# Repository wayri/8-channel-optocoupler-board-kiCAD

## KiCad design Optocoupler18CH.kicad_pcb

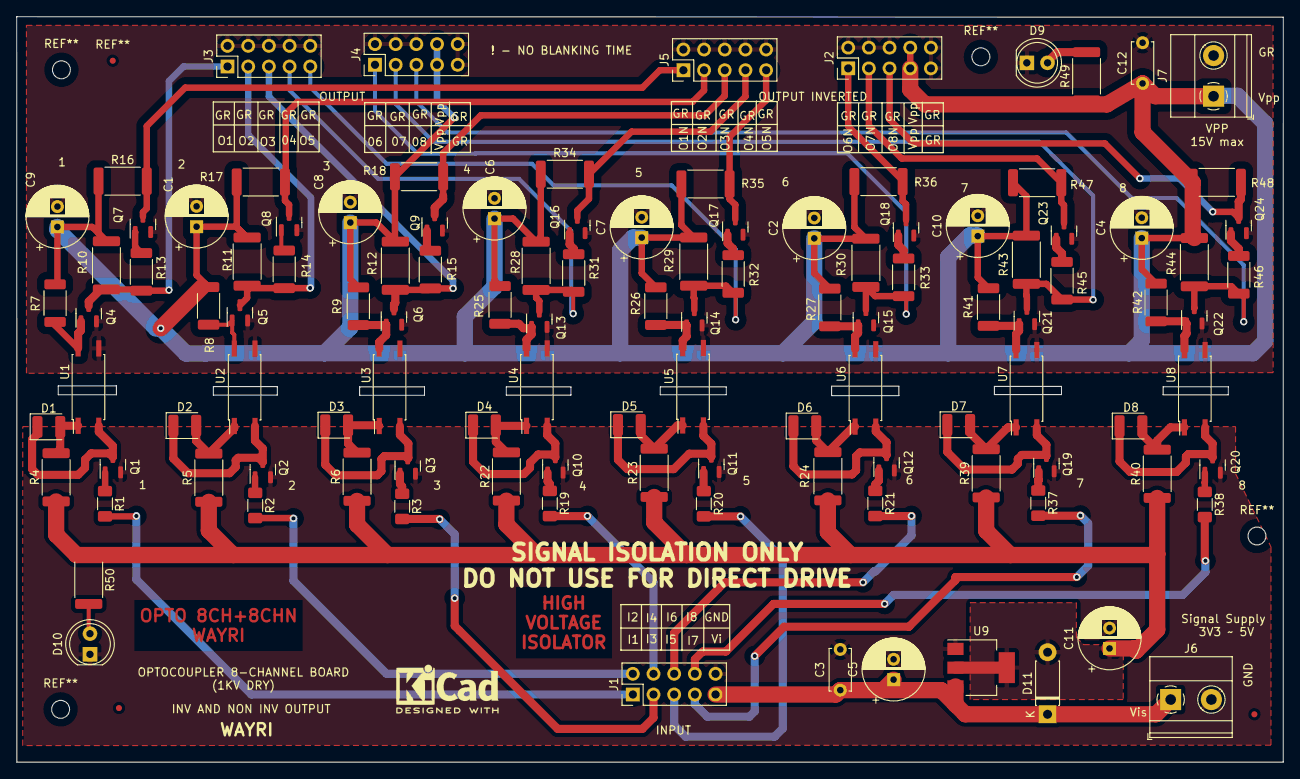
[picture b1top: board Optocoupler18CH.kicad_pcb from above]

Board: 2 copper layers, 155.6 x 91.6 mm, 113 parts (0 on the bottom side), 71 nets.

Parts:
C1, C2, C4, C6, C7, C8, C9, C10: 10uF 25V; CP_Radial_D7.5mm_P2.50mm
C3: Cfi; C_Disc_D5.0mm_W2.5mm_P5.00mm
C5: Ci 100uF 25V; CP_Radial_D7.5mm_P2.50mm
C11: Co; CP_Radial_D7.5mm_P2.50mm
C12: 100n; C_Disc_D5.0mm_W2.5mm_P5.00mm
D1, D2, D3, D4, D5, D6, D7, D8: LED; LED_1210_3225Metric
D9: LED RED; LED_D5.0mm
D10: LED GREEN; LED_D5.0mm
D11: 1.5KExxA; D_DO-41_SOD81_P7.62mm_Horizontal
J1: INPUT; PinHeader_2x05_P2.54mm_Vertical
J2, J5: CHN; PinHeader_2x05_P2.54mm_Vertical
J3, J4: CH; PinHeader_2x05_P2.54mm_Vertical
J6: Vsi; TerminalBlock_Phoenix_MKDS-1,5-2_1x02_P5.00mm_Horizontal
J7: Vp; TerminalBlock_Phoenix_MKDS-1,5-2_1x02_P5.00mm_Horizontal
Q1, Q2, Q3, Q4, Q5, Q6, Q7, Q8, Q9, Q10, Q11, Q12, Q13, Q14, Q15, Q16, Q17, Q18, Q19, Q20, Q21, Q22, Q23, Q24: BC847B; SOT-23
R1, R2, R3, R19, R20, R21, R37, R38: 10k; R_1206_3216Metric_Pad1.30x1.75mm_HandSolder
R4, R5, R6, R10, R11, R12, R16, R17, R18, R22, R23, R24, R28, R29, R30, R34, R35, R36, R39, R40, R43, R44, R47, R48, R49, R50: 300 0.5W; R_2512_6332Metric
R7, R8, R9, R13, R14, R15, R25, R26, R27, R31, R32, R33, R41, R42, R45, R46: 10k 0.25W; R_2010_5025Metric
U1, U2, U3, U4, U5, U6, U7, U8: EL817; SO-4_7.6x3.6mm_P2.54mm
U9: AMS1117-5.0; SOT-223-3_TabPin2

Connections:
5V: C11.1, D11.2 (A2), R4.1, R5.1, R6.1, R22.1, R23.1, R24.1, R39.1, R40.1, R50.1, U9.2 (VO)
GND: C3.2, C5.2, C11.2, D10.1 (K), J1.10, J6.2, Q1.2 (E), Q2.2 (E), Q3.2 (E), Q10.2 (E), Q11.2 (E), Q12.2 (E), Q19.2 (E), Q20.2 (E), U9.1 (GND)
GREF: C1.2, C2.2, C4.2, C6.2, C7.2, C8.2, C9.2, C10.2, C12.2, D9.1 (K), J2.2, J2.4, J2.6, J2.9, J2.10, J3.2, J3.4, J3.6, J3.8, J3.10, J4.2, J4.4, J4.6, J4.9, J4.10, J5.2, J5.4, J5.6, J5.8, J5.10, J7.2, Q4.2 (E), Q5.2 (E), Q6.2 (E), Q7.2 (E), Q8.2 (E), Q9.2 (E), Q13.2 (E), Q14.2 (E), Q15.2 (E), Q16.2 (E), Q17.2 (E), Q18.2 (E), Q21.2 (E), Q22.2 (E), Q23.2 (E), Q24.2 (E), U1.3, U2.3, U3.3, U4.3, U5.3, U6.3, U7.3, U8.3
unnamed: D1.1 (K), Q1.3 (C), U1.2
unnamed: D1.2 (A), R4.2, U1.1
unnamed: D2.1 (K), Q2.3 (C), U2.2
unnamed: D2.2 (A), R5.2, U2.1
unnamed: D3.1 (K), Q3.3 (C), U3.2
unnamed: D3.2 (A), R6.2, U3.1
unnamed: D4.1 (K), Q10.3 (C), U4.2
unnamed: D4.2 (A), R22.2, U4.1
unnamed: D5.1 (K), Q11.3 (C), U5.2
unnamed: D5.2 (A), R23.2, U5.1
unnamed: D6.1 (K), Q12.3 (C), U6.2
unnamed: D6.2 (A), R24.2, U6.1
unnamed: D7.1 (K), Q19.3 (C), U7.2
unnamed: D7.2 (A), R39.2, U7.1
unnamed: D8.1 (K), Q20.3 (C), U8.2
unnamed: D8.2 (A), R40.2, U8.1
unnamed: D9.2 (A), R49.2
unnamed: D10.2 (A), R50.2
unnamed: Q1.1 (B), R1.1
unnamed: Q2.1 (B), R2.1
unnamed: Q3.1 (B), R3.1
unnamed: Q4.1 (B), R7.2, U1.4
unnamed: Q5.1 (B), R8.2, U2.4
unnamed: Q6.1 (B), R9.2, U3.4
unnamed: Q7.1 (B), R13.2
unnamed: Q8.1 (B), R14.2
unnamed: Q9.1 (B), R15.2
unnamed: Q10.1 (B), R19.1
unnamed: Q11.1 (B), R20.1
unnamed: Q12.1 (B), R21.1
unnamed: Q13.1 (B), R25.2, U4.4
unnamed: Q14.1 (B), R26.2, U5.4
unnamed: Q15.1 (B), R27.2, U6.4
unnamed: Q16.1 (B), R31.2
unnamed: Q17.1 (B), R32.2
unnamed: Q18.1 (B), R33.2
unnamed: Q19.1 (B), R37.1
unnamed: Q20.1 (B), R38.1
unnamed: Q21.1 (B), R41.2, U7.4
unnamed: Q22.1 (B), R42.2, U8.4
unnamed: Q23.1 (B), R45.2
unnamed: Q24.1 (B), R46.2
Vi1: J1.1, R1.2
Vi2: J1.2, R2.2
Vi3: J1.3, R3.2
Vi4: J1.4, R19.2
Vi5: J1.5, R20.2
Vi6: J1.6, R21.2
Vi7: J1.7, R37.2
Vi8: J1.8, R38.2
Vis: C3.1, C5.1, D11.1 (A1), J1.9, J6.1, U9.3 (VI)
Vo1: J3.1, Q4.3 (C), R10.2, R13.1
Vo1n: J5.1, Q7.3 (C), R16.2
Vo2: J3.3, Q5.3 (C), R11.2, R14.1
Vo2n: J5.3, Q8.3 (C), R17.2
Vo3: J3.5, Q6.3 (C), R12.2, R15.1
Vo3n: J5.5, Q9.3 (C), R18.2
Vo4: J3.7, Q13.3 (C), R28.2, R31.1
Vo4n: J5.7, Q16.3 (C), R34.2
Vo5: J3.9, Q14.3 (C), R29.2, R32.1
Vo5n: J5.9, Q17.3 (C), R35.2
Vo6: J4.1, Q15.3 (C), R30.2, R33.1
Vo6n: J2.1, Q18.3 (C), R36.2
Vo7: J4.3, Q21.3 (C), R43.2, R45.1
Vo7n: J2.3, Q23.3 (C), R47.2
Vo8: J4.5, Q22.3 (C), R44.2, R46.1
Vo8n: J2.5, Q24.3 (C), R48.2
Vpp: C1.1, C2.1, C4.1, C6.1, C7.1, C8.1, C9.1, C10.1, C12.1, J2.7, J2.8, J4.7, J4.8, J7.1, R7.1, R8.1, R9.1, R10.1, R11.1, R12.1, R16.1, R17.1, R18.1, R25.1, R26.1, R27.1, R28.1, R29.1, R30.1, R34.1, R35.1, R36.1, R41.1, R42.1, R43.1, R44.1, R47.1, R48.1, R49.1

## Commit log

2022-09-07 All original kiCAD files
